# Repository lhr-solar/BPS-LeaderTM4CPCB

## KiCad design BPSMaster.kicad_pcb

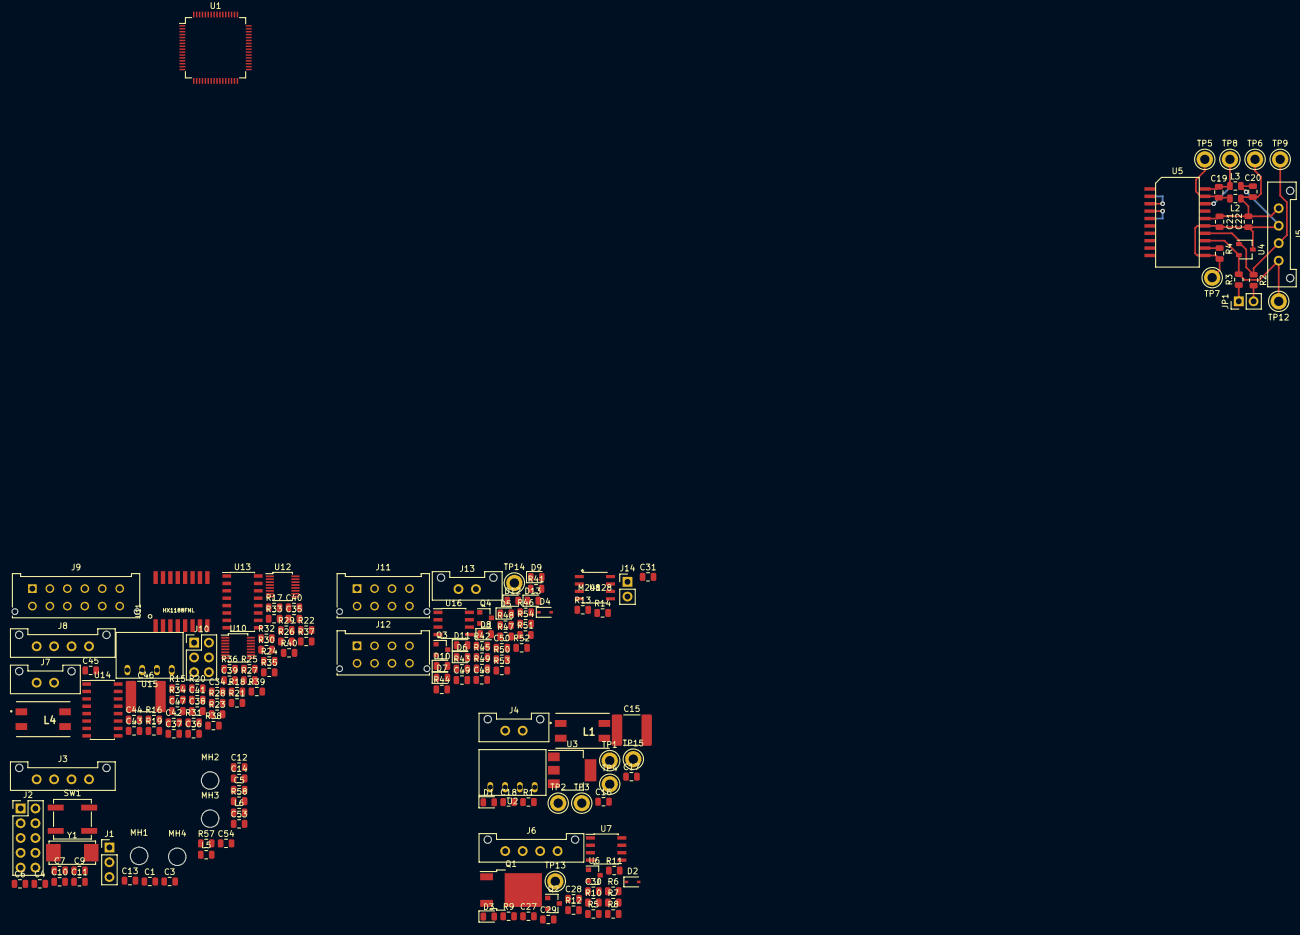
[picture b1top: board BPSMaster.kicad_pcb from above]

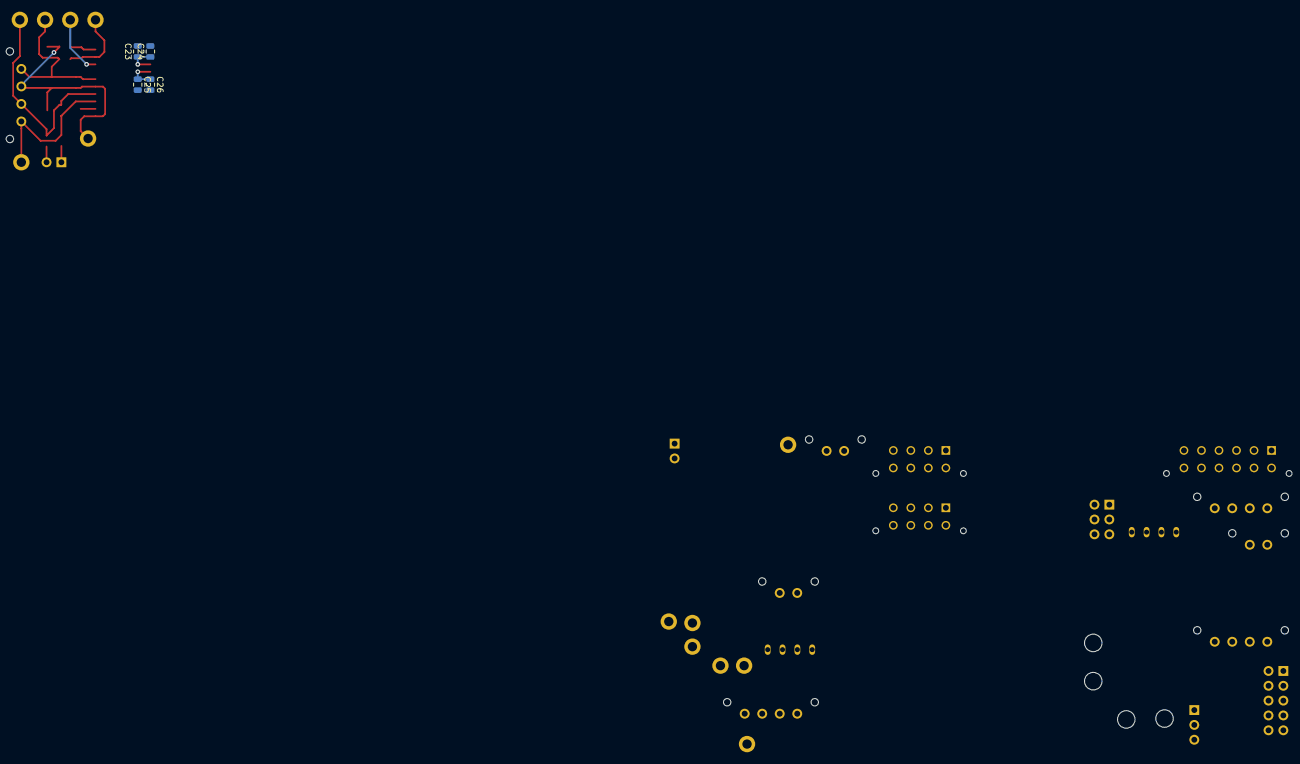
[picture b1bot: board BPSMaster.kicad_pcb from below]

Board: 2 copper layers, 176 parts (4 on the bottom side), 126 nets.

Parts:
C1, C3, C4, C5, C6, C9, C11, C12, C21, C24, C25, C29, C31, C36, C38, C40, C41, C42, C43, C44, C45, C50: 0.1uF; C_0805_2012Metric
C7, C16, C47: 4.7uF; C_0805_2012Metric
C10, C27, C30, C48, C53, C54: 1uF; C_0805_2012Metric
C13, C14: 6pF; C_0805_2012Metric
C15, C46: 470pF; C_2220_5650Metric
C17, C18, C20, C23, C28, C49: 10uF; C_0805_2012Metric
C19: 0.22uF; C_0805_2012Metric
C22, C26, C34, C35, C37, C39: 0.01uF; C_0805_2012Metric
D1: PowerOn; LED_0805_2012Metric
D2, D4: 1N4148WS; D_SOD-323
D3: ContactorEn; LED_0805_2012Metric
D5: Fault; LED_0805_2012Metric
D6: Heartbeat; LED_0805_2012Metric
D7: UVolt; LED_0805_2012Metric
D8: OVolt; LED_0805_2012Metric
D9: OTemp; LED_0805_2012Metric
D10: OCurr; LED_0805_2012Metric
D11: WDError; LED_0805_2012Metric
D12: CANError; LED_0805_2012Metric
D13: Extra; LED_0805_2012Metric
J1: SWD; PinHeader_1x03_P2.54mm_Vertical
J2: Logic Analyzer; PinHeader_2x05_P2.54mm_Vertical
J3: CurrentSlaveConnector; Molex_MicroFit3.0_1x4xP3.00mm_PolarizingPeg_Vertical
J4: CarPowerConnector; Molex_MicroFit3.0_1x2xP3.00mm_PolarizingPeg_Vertical
J5: CAN_Out; Molex_MicroFit3.0_1x4xP3.00mm_PolarizingPeg_Vertical
J6: ContactorConnector; Molex_MicroFit3.0_1x4xP3.00mm_PolarizingPeg_Vertical
J7: VoltageSlaveConnector; Molex_MicroFit3.0_1x2xP3.00mm_PolarizingPeg_Vertical
J8: DisplayConnector; Molex_MicroFit3.0_1x4xP3.00mm_PolarizingPeg_Vertical
J9: TempSlaveConnector; Molex_MicroFit3.0_2x6xP3.00mm_PolarizingPeg_Vertical
J10: DisplayJumper; PinHeader_2x03_P2.54mm_Vertical
J11: FrontFans; Molex_MicroFit3.0_2x4xP3.00mm_PolarizingPeg_Vertical
J12: BackFans; Molex_MicroFit3.0_2x4xP3.00mm_PolarizingPeg_Vertical
J13: ErrorLightConnector; Molex_MicroFit3.0_1x2xP3.00mm_PolarizingPeg_Vertical
J14: Conn_01x03; PinHeader_1x02_P2.54mm_Vertical
JP1: Termination Resistors; PinHeader_1x02_P2.54mm_Vertical
L1, L4: 10uH; SRF0905A
L2, L3: 2kH; L_0805_2012Metric
L5, L6: 600; L_0805_2012Metric
MH1, MH2, MH3, MH4: MountingHole; MountingHole_3mm
Q1: VND5N07-E; TO-252-2
Q2, Q3, Q4: NTR4003NT1G; SOT-23
R1, R5: 1.5k; R_0805_2012Metric
R2, R3: 60; R_0805_2012Metric
R4, R9, R11, R43, R45: 0; R_0805_2012Metric
R6, R13, R14: 4.7k; R_0805_2012Metric
R7, R42: 470; R_0805_2012Metric
R8: 1k; R_0805_2012Metric
R10, R12, R44, R46: 10k; R_0805_2012Metric
R15, R18, R19, R20: 49.9; R_0805_2012Metric
R16, R21: 806; R_0805_2012Metric
R17, R22: 1.21k; R_0805_2012Metric
R23, R24, R25, R26, R27, R28, R29, R30, R31, R32, R33, R34, R35, R36, R37, R38, R39, R40: 50; R_0805_2012Metric
R41: 1.6k; R_0805_2012Metric
R47: 680; R_0805_2012Metric
R48, R49, R50, R51, R52, R53, R54: 750; R_0805_2012Metric
R57, R58: 220k; R_0805_2012Metric
SW1: B3SL-1002P; SW_SPST_B3SL-1002P
TP1: +12V_TP; TestPoint_Keystone_5005-5009_Compact
TP2: +5V_TP; TestPoint_Keystone_5005-5009_Compact
TP3: GND_TP; TestPoint_Keystone_5005-5009_Compact
TP4: +3.3V_TP; TestPoint_Keystone_5005-5009_Compact
TP5: CAN_ISO_Vout; TestPoint_Keystone_5005-5009_Compact
TP6: CAN_ISO_Vin; TestPoint_Keystone_5005-5009_Compact
TP7: CAN_ISO_GndIn; TestPoint_Keystone_5005-5009_Compact
TP8: CAN_ISO_GndOut; TestPoint_Keystone_5005-5009_Compact
TP9: CAN_H; TestPoint_Keystone_5005-5009_Compact
TP12: CAN_L; TestPoint_Keystone_5005-5009_Compact
TP13: ContactorGate_TP; TestPoint_Keystone_5005-5009_Compact
TP14: StrobeLightGate_TP; TestPoint_Keystone_5005-5009_Compact
TP15: GNDPWR_TP; TestPoint_Keystone_5005-5009_Compact
U1: TM4C123GH6PM; LQFP-64_10x10mm_P0.5mm
U2, U15: RI3-1205S; RI3_DC_Converter
U3: NCP1117-3.3_SOT223; SOT-223-3_TabPin2
U4: CDSOT23-T24CAN; SOT-23W
U5: ADM3055E; SOIC-20W_7.5x15.4mm_Pitch1.27mm
U6: BAS70-04; SOT-23
U7, U16: SI8261ABC-IS; SOIC-8_3.9x4.9mm_P1.27mm
U8: M24128; M24128-BRMN6P
U10, U12: LTC6820; MSOP-16_3x4mm_P0.5mm
U11: HX1188FNL; HXXXX
U13: Si8641EC-B-IS1; SOIC-16_3.9x9.9mm_P1.27mm
U14: SI8660EC-B-IS1; SOIC-16_3.9x9.9mm_P1.27mm
Y1: NX8045GB-8.000M-STD-CSJ-1

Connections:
+3V3: C1.1, C3.1, C4.1, C5.1, C6.1, C7.1, C9.1, C10.1, C18.1, C25.1, C26.1, C31.1, C36.1, C42.1, J10.1, J10.2, R13.1, R14.1, TP4.1, U1.2, U1.11, U1.25, U1.26, U1.37, U1.42, U1.54, U1.56, U3.2, U5.4, U8.8, U10.6, U10.7, U10.8, U12.6
+5V: C12.2, C15.2, C17.1, C23.1, C24.1, C38.1, C40.1, C43.1, C44.1, D5.2, J3.1, R1.1, R5.1, R6.2, R7.2, R42.2, TP2.1, U2.4, U3.3, U5.3, U6.2, U10.9, U10.12, U12.9, U12.12, U13.1, U13.7, U14.1
+5VL: C41.1, C45.1, C46.2, J9.1, U13.10, U13.16, U14.16, U15.4
+12V: C16.1, C27.2, C28.1, C29.1, C47.1, C48.2, C49.1, C50.1, D2.1, D4.1, J4.1, J6.1, J8.3, J11.1, J11.2, J11.3, J11.4, J12.1, J12.2, J12.3, J12.4, J13.1, L1.1, L1.2, L4.1, L4.2, TP1.1, U7.8, U16.8
/AIN10: C53.1, R57.2, U1.58
/AIN11: C54.1, R58.2, U1.57
/CAN1_RX: J2.4, U1.17, U5.5
/CAN1_TX: J2.2, U1.18, U5.7
/CAN/CAN_H: J5.3, R2.2, TP9.1, U4.1, U5.14
/CAN/CAN_L: J5.4, R3.2, TP12.1, U4.2, U5.13
/CAN/RSlope: R4.1, U5.12
/CAN/TERM_H: JP1.2, R2.1
/CAN/TERM_L: JP1.1, R3.1
/Contactor Driver/CONTACTOR_V-: D2.2, J6.2, Q1.2
/DISPLAY_CS: U1.20, U12.5
/FAULT: R45.2, U1.1
/I2C3_SCL: J14.1, R13.2, U1.61, U8.6
/I2C3_SDA: J14.2, R14.2, U1.62, U8.5
/LTC6811_CS: U1.31, U10.5
/NRST: C11.1, SW1.1, U1.38
/OSC_IN: C14.1, U1.40, Y1.2
/OSC_OUT: C13.1, U1.41, Y1.1
/PA4: D10.2, U1.21
/PA5: D9.2, U1.22
/PA6: D8.2, U1.23
/PA7: D7.2, U1.24
/PD2: R11.2, U1.63
/PD3: C30.1, R8.1, U1.64, U6.3
/PD6: D13.2, U1.53
/PE4: D12.2, U1.59
/PE5: D11.2, U1.60
/RUN: D6.2, U1.48
/SPI1_CLK: J2.6, R23.2, U1.30, U10.4, U12.4
/SPI1_MISO: J2.8, R27.2, U1.28, U10.3, U12.3
/SPI1_MOSI: J2.10, R25.2, U1.29, U10.2, U12.2
/SPI/CS1: J9.12, R30.1
/SPI/CS2: J9.11, R32.1
/SPI/CS3: J9.10, R34.1
/SPI/CS4: J9.9, R36.1
/SPI/CS5: J9.8, R38.1
/SPI/CS6: J9.7, R40.1
/SPI/DISP_IM: R18.1, U11.8, U12.10
/SPI/DISP_IP: R15.1, U11.6, U12.11
/SPI/DISP_PHA: J10.4, U12.8
/SPI/DISP_POL: J10.3, U12.7
/SPI/VOLT_IM: R20.1, U10.10, U11.3
/SPI/VOLT_IP: R19.1, U10.11, U11.1
/SWCLK: J1.3, U1.52
/SWDIO: J1.2, U1.51
/TEMP_CS1: R29.1, U1.4
/TEMP_CS2: R31.1, U1.5
/TEMP_CS3: R33.1, U1.6
/TEMP_CS4: R35.1, U1.7
/TEMP_CS5: R37.1, U1.8
/TEMP_CS6: R39.1, U1.9
/UART1_RX: J2.5, U1.16
/UART1_TX: J2.3, U1.15
GND: C1.2, C3.2, C4.2, C5.2, C6.2, C7.2, C9.2, C10.2, C11.2, C12.1, C13.2, C14.2, C17.2, C18.2, C23.2, C24.2, C25.2, C26.2, C30.2, C31.2, C34.2, C35.2, C36.2, C37.2, C38.2, C39.2, C40.2, C42.2, C43.2, C44.2, C53.2, C54.2, D1.1, J1.1, J2.1, J3.2, J6.3, J10.5, J10.6, Q2.2, Q4.2, R12.2, R17.1, R22.1, R46.2, R47.2, R48.2, R49.2, R50.2, R51.2, R52.2, R53.2, R54.2, SW1.2, TP3.1, U1.3, U1.12, U1.27, U1.32, U1.35, U1.39, U1.55, U2.3, U3.1, U5.1, U5.2, U5.10, U6.1, U8.1, U8.2, U8.3, U8.4, U8.7, U10.1, U10.13, U10.14, U12.1, U12.13, U12.14, U13.2, U13.8, U14.8
GNDPWR: C16.2, C27.1, C28.2, C29.2, C47.2, C48.1, C49.2, C50.2, J4.2, J8.4, J11.5, J11.6, J11.7, J11.8, J12.5, J12.6, J12.7, J12.8, Q1.3, Q3.2, R10.2, R44.2, TP15.1, U2.1, U7.5, U15.1, U16.5
GND_A: C41.2, C45.2, J9.5, J9.6, U13.9, U13.15, U14.9, U15.3
unnamed: C15.1, L1.3, L1.4, U2.2
unnamed: C19.1, L2.2, TP5.1, U5.19
unnamed: C19.2, L3.2, TP8.1, U5.18, U5.20
unnamed: C20.1, C21.1, C22.1, J5.1, L2.1, TP6.1, U5.16
unnamed: C20.2, C21.2, C22.2, J5.2, L3.1, R4.2, TP7.1, U4.3, U5.11, U5.15
unnamed: C34.1, U11.7
unnamed: C35.1, R15.2, R18.2
unnamed: C37.1, U11.2
unnamed: C39.1, R19.2, R20.2
unnamed: C46.1, L4.3, L4.4, U15.2
unnamed: D1.2, R1.2
unnamed: D3.1, Q2.3, U7.3
unnamed: D3.2, R5.2
unnamed: D4.2, J13.2, Q3.3
unnamed: D5.1, R41.1
unnamed: D6.1, R47.1
unnamed: D7.1, R48.1
unnamed: D8.1, R49.1
unnamed: D9.1, R50.1
unnamed: D10.1, R51.1
unnamed: D11.1, R52.1
unnamed: D12.1, R53.1
unnamed: D13.1, R54.1
unnamed: J3.3, L5.1
unnamed: J3.4, L6.1
unnamed: J6.4, R6.1, R8.2
unnamed: J7.1, U11.16
unnamed: J7.2, U11.14
unnamed: J8.1, U11.11
unnamed: J8.2, U11.9
unnamed: J9.2, R24.2
unnamed: J9.3, R26.2
unnamed: J9.4, R28.2
unnamed: L5.2, R57.1
unnamed: L6.2, R58.1
unnamed: Q1.1, R9.1, R10.1
unnamed: Q2.1, R11.1, R12.1
unnamed: Q3.1, R43.1, R44.1
unnamed: Q4.1, R45.1, R46.1
unnamed: Q4.3, R41.2, U16.3
unnamed: R7.1, U7.2
unnamed: R9.2, TP13.1, U7.6
unnamed: R16.1, R17.2, U10.15
unnamed: R16.2, U10.16
unnamed: R21.1, R22.2, U12.15
unnamed: R21.2, U12.16
unnamed: R23.1, U13.3
unnamed: R24.1, U13.14
unnamed: R25.1, U13.4
unnamed: R26.1, U13.13
unnamed: R27.1, U13.6
unnamed: R28.1, U13.11
unnamed: R29.2, U14.2
unnamed: R30.2, U14.15
unnamed: R31.2, U14.3
unnamed: R32.2, U14.14
unnamed: R33.2, U14.4
unnamed: R34.2, U14.13
unnamed: R35.2, U14.5
unnamed: R36.2, U14.12
unnamed: R37.2, U14.6
unnamed: R38.2, U14.11
unnamed: R39.2, U14.7
unnamed: R40.2, U14.10
unnamed: R42.1, U16.2
unnamed: R43.2, TP14.1, U16.6

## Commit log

2020-08-02 Set up for own repository
2020-10-03 Adds QuAC

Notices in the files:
parts and their libraries:
Copyright 2016 Accelerated Designs. All rights reserved.
